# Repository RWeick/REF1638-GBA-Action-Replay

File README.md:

# REF1638-GBA-Action-Replay
The kicad files and firmware from the Datel GBA Action Replay board revision REF1638

PCB Thickness: 0.8 mm

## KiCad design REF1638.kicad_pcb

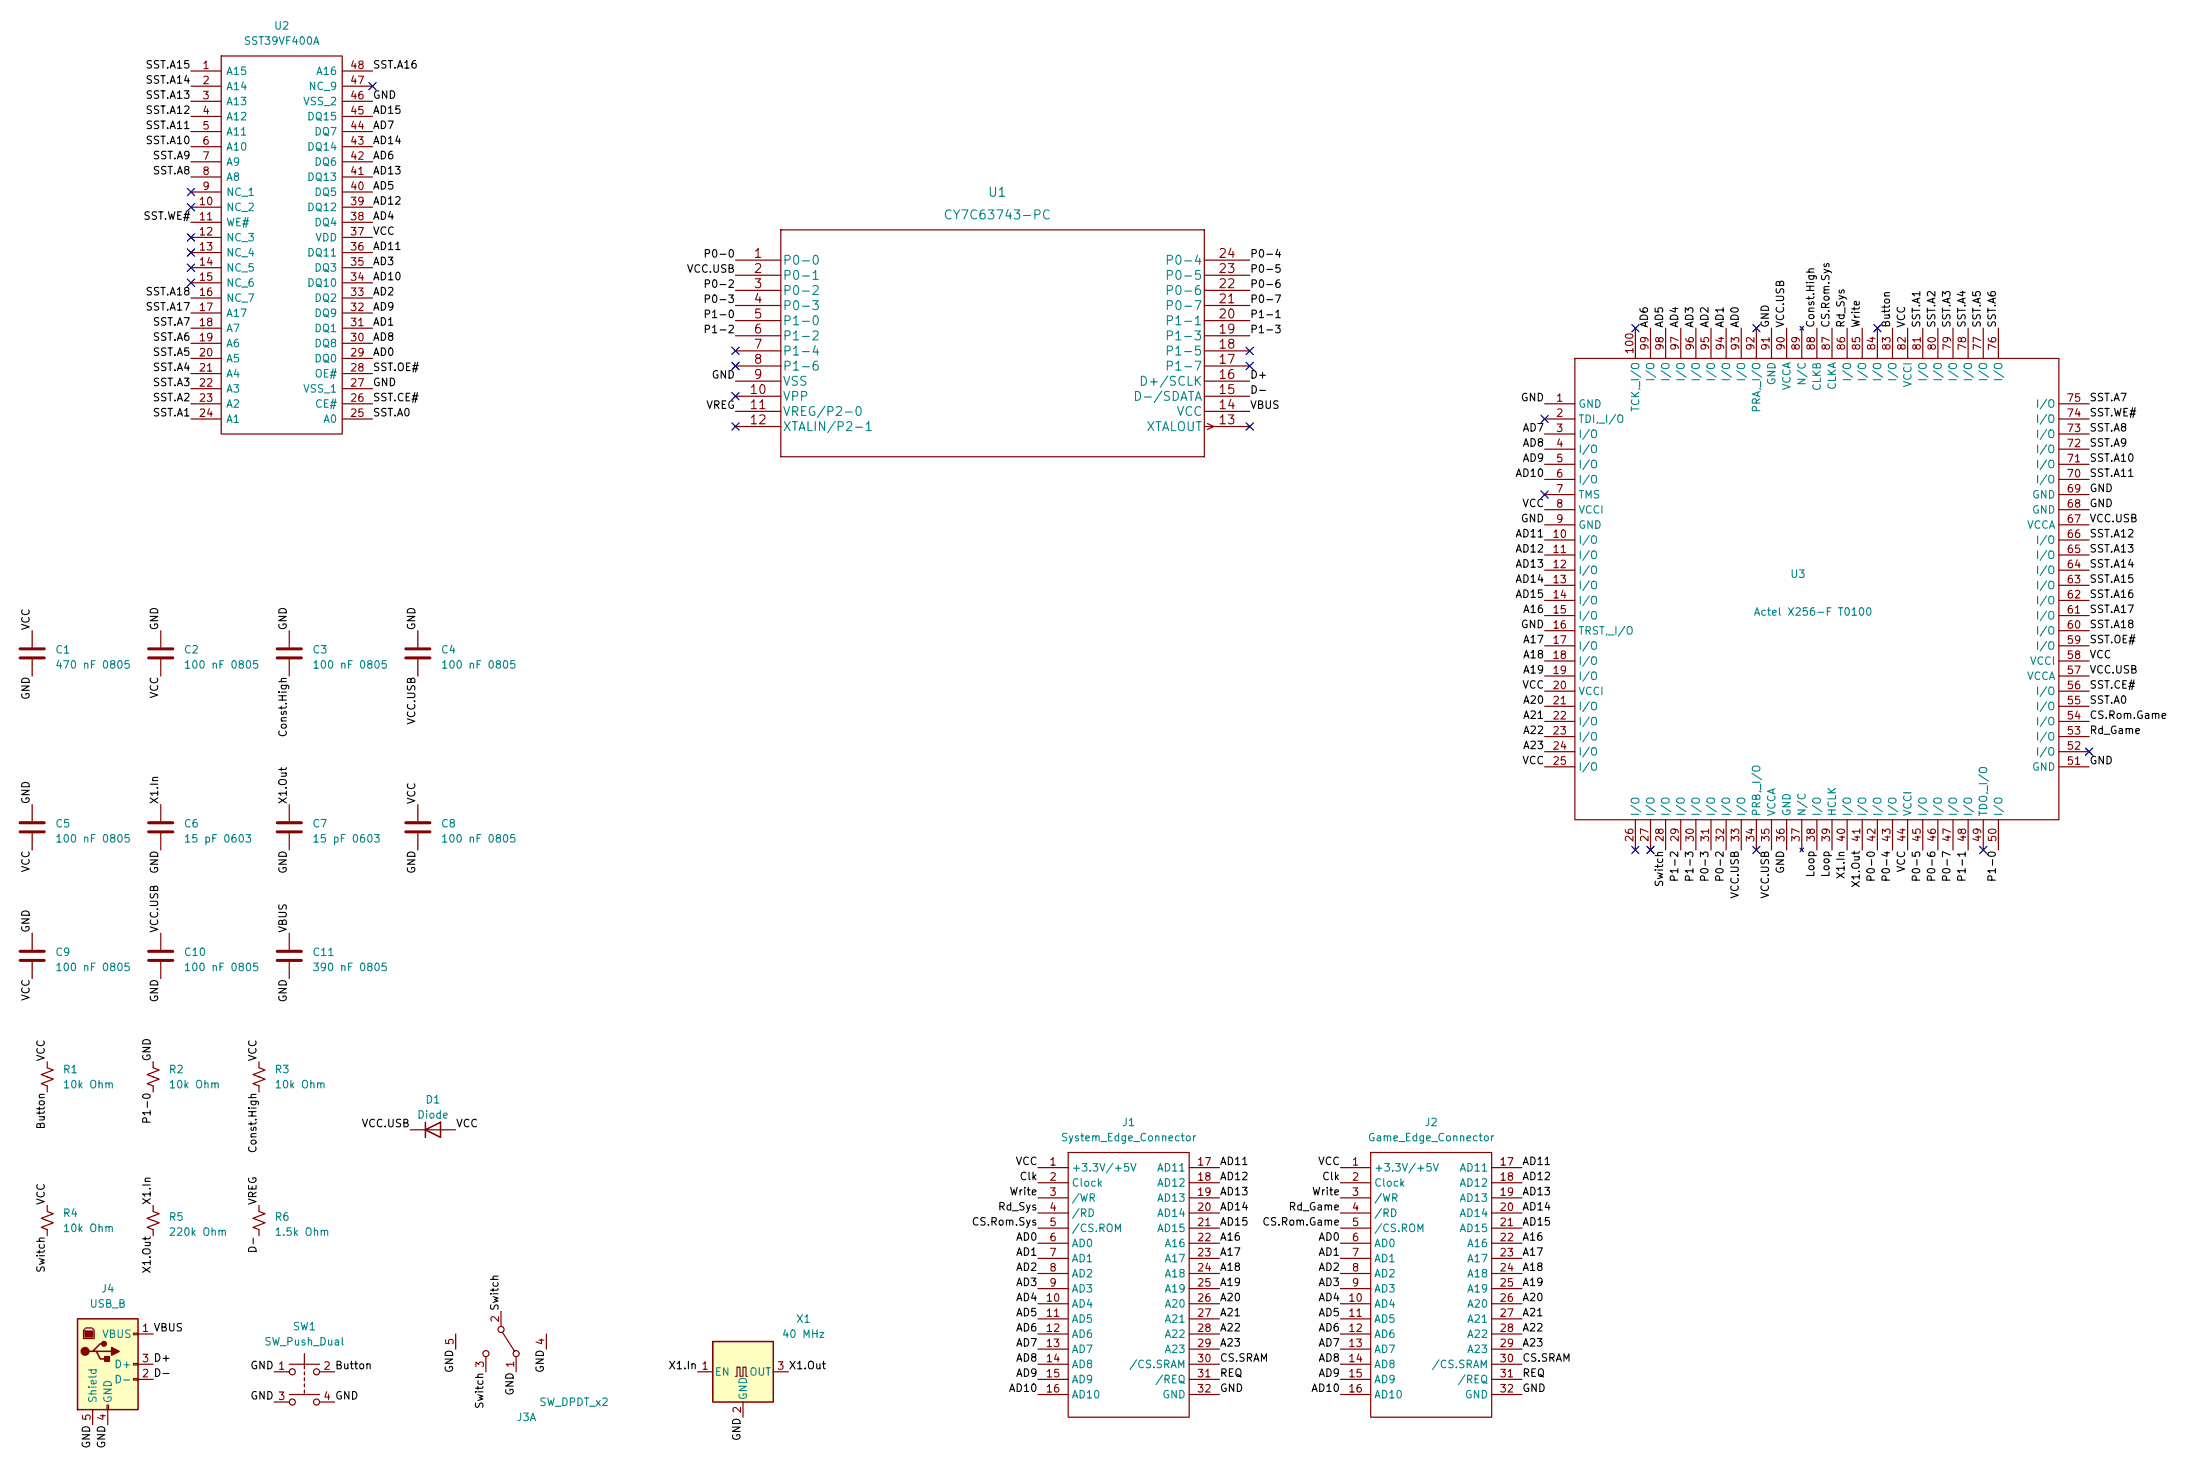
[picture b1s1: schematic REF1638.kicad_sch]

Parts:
C1: 470 nF 0805; Small SMD
C2, C3, C4, C5, C8, C9, C10: 100 nF 0805; Small SMD
C6, C7: 15 pF 0603; 0603 Caps
C11: 390 nF 0805; Small SMD
D1: Diode
J1: System_Edge_Connector; Edge Connector
J2: Game_Edge_Connector; Cartridge Slot, GBA
J3: SW_DPDT_x2; Switch_Wide
J4: USB_B; USB_B_OST_USB-B1HSxx_Horizontal
R1, R2, R3, R4: 10k Ohm; Small SMD
R5: 220k Ohm; Small SMD
R6: 1.5k Ohm; Small SMD
SW1: SW_Push_Dual; 1mm Side Push Button
U1: CY7C63743-PC; CY7C63743
U2: SST39VF400A; SST 39VF400A; Manufacturer_Part_Number SST39VF200A-70-4C-EKE
U3: Actel X256-F T0100; Actel X256-F
X1: 40 MHz; Crystal

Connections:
/A16: J1.22 (A16), J2.22 (A16), U3.15 (I/O)
/A17: J1.23 (A17), J2.23 (A17), U3.17 (I/O)
/A18: J1.24 (A18), J2.24 (A18), U3.18 (I/O)
/A19: J1.25 (A19), J2.25 (A19), U3.19 (I/O)
/A20: J1.26 (A20), J2.26 (A20), U3.21 (I/O)
/A21: J1.27 (A21), J2.27 (A21), U3.22 (I/O)
/A22: J1.28 (A22), J2.28 (A22), U3.23 (I/O)
/A23: J1.29 (A23), J2.29 (A23), U3.24 (I/O)
/AD0: J1.6 (AD0), J2.6 (AD0), U2.29 (DQ0), U3.93 (I/O)
/AD1: J1.7 (AD1), J2.7 (AD1), U2.31 (DQ1), U3.94 (I/O)
/AD2: J1.8 (AD2), J2.8 (AD2), U2.33 (DQ2), U3.95 (I/O)
/AD3: J1.9 (AD3), J2.9 (AD3), U2.35 (DQ3), U3.96 (I/O)
/AD4: J1.10 (AD4), J2.10 (AD4), U2.38 (DQ4), U3.97 (I/O)
/AD5: J1.11 (AD5), J2.11 (AD5), U2.40 (DQ5), U3.98 (I/O)
/AD6: J1.12 (AD6), J2.12 (AD6), U2.42 (DQ6), U3.99 (I/O)
/AD7: J1.13 (AD7), J2.13 (AD7), U2.44 (DQ7), U3.3 (I/O)
/AD8: J1.14 (AD8), J2.14 (AD8), U2.30 (DQ8), U3.4 (I/O)
/AD9: J1.15 (AD9), J2.15 (AD9), U2.32 (DQ9), U3.5 (I/O)
/AD10: J1.16 (AD10), J2.16 (AD10), U2.34 (DQ10), U3.6 (I/O)
/AD11: J1.17 (AD11), J2.17 (AD11), U2.36 (DQ11), U3.10 (I/O)
/AD12: J1.18 (AD12), J2.18 (AD12), U2.39 (DQ12), U3.11 (I/O)
/AD13: J1.19 (AD13), J2.19 (AD13), U2.41 (DQ13), U3.12 (I/O)
/AD14: J1.20 (AD14), J2.20 (AD14), U2.43 (DQ14), U3.13 (I/O)
/AD15: J1.21 (AD15), J2.21 (AD15), U2.45 (DQ15), U3.14 (I/O)
/Button: R1.2, SW1.2, U3.83 (I/O)
/CS.Rom.Game: J2.5 (/CS.ROM), U3.54 (I/O)
/CS.Rom.Sys: J1.5 (/CS.ROM), U3.87 (CLKA)
/CS.SRAM: J1.30 (/CS.SRAM), J2.30 (/CS.SRAM)
/Clk: J1.2 (Clock), J2.2 (Clock)
/Const.High: C3.2, R3.2, U3.88 (CLKB)
/D+: J4.3 (D+), U1.16 (D+/SCLK)
/D-: J4.2 (D-), R6.2, U1.15 (D-/SDATA)
/GND: C1.2, C2.1, C3.1, C4.1, C5.1, C6.2, C7.2, C8.2, C9.1, C10.2, C11.2, J1.32 (GND), J2.32 (GND), J3.1 (A), J3.4 (Case_GND), J3.5 (Case_GND), J4.4 (GND), J4.5 (Shield), R2.1, SW1.1, SW1.3, SW1.4, U1.9 (VSS), U2.27 (VSS_1), U2.46 (VSS_2), U3.1 (GND), U3.9 (GND), U3.16 (TRST,_I/O), U3.36 (GND), U3.51 (GND), U3.68 (GND), U3.69 (GND), U3.91 (GND), X1.2 (GND)
/Loop: U3.38 (I/O), U3.39 (HCLK)
/P0-0: U1.1 (P0-0), U3.42 (I/O)
/P0-2: U1.3 (P0-2), U3.32 (I/O)
/P0-3: U1.4 (P0-3), U3.31 (I/O)
/P0-4: U1.24 (P0-4), U3.43 (I/O)
/P0-5: U1.23 (P0-5), U3.45 (I/O)
/P0-6: U1.22 (P0-6), U3.46 (I/O)
/P0-7: U1.21 (P0-7), U3.47 (I/O)
/P1-0: R2.2, U1.5 (P1-0), U3.50 (I/O)
/P1-1: U1.20 (P1-1), U3.48 (I/O)
/P1-2: U1.6 (P1-2), U3.29 (I/O)
/P1-3: U1.19 (P1-3), U3.30 (I/O)
/REQ: J1.31 (/REQ), J2.31 (/REQ)
/Rd_Game: J2.4 (/RD), U3.53 (I/O)
/Rd_Sys: J1.4 (/RD), U3.86 (I/O)
/SST.A0: U2.25 (A0), U3.55 (I/O)
/SST.A1: U2.24 (A1), U3.81 (I/O)
/SST.A2: U2.23 (A2), U3.80 (I/O)
/SST.A3: U2.22 (A3), U3.79 (I/O)
/SST.A4: U2.21 (A4), U3.78 (I/O)
/SST.A5: U2.20 (A5), U3.77 (I/O)
/SST.A6: U2.19 (A6), U3.76 (I/O)
/SST.A7: U2.18 (A7), U3.75 (I/O)
/SST.A8: U2.8 (A8), U3.73 (I/O)
/SST.A9: U2.7 (A9), U3.72 (I/O)
/SST.A10: U2.6 (A10), U3.71 (I/O)
/SST.A11: U2.5 (A11), U3.70 (I/O)
/SST.A12: U2.4 (A12), U3.66 (I/O)
/SST.A13: U2.3 (A13), U3.65 (I/O)
/SST.A14: U2.2 (A14), U3.64 (I/O)
/SST.A15: U2.1 (A15), U3.63 (I/O)
/SST.A16: U2.48 (A16), U3.62 (I/O)
/SST.A17: U2.17 (A17), U3.61 (I/O)
/SST.A18: U2.16 (NC_7), U3.60 (I/O)
/SST.CE#: U2.26 (CE#), U3.56 (I/O)
/SST.OE#: U2.28 (OE#), U3.59 (I/O)
/SST.WE#: U2.11 (WE#), U3.74 (I/O)
/Switch: J3.2 (B), J3.3 (C), R4.2, U3.28 (I/O)
/VBUS: C11.1, J4.1 (VBUS), U1.14 (VCC)
/VCC: C1.1, C2.2, C5.2, C8.1, C9.2, D1.2 (A), J1.1 (+3.3V/+5V), J2.1 (+3.3V/+5V), R1.1, R3.1, R4.1, U2.37 (VDD), U3.8 (VCCI), U3.20 (VCCI), U3.25 (I/O), U3.44 (VCCI), U3.58 (VCCI), U3.82 (VCCI)
/VCC.USB: C4.2, C10.1, D1.1 (K), U1.2 (P0-1), U3.33 (I/O), U3.35 (VCCA), U3.57 (VCCA), U3.67 (VCCA), U3.90 (VCCA)
/VREG: R6.1, U1.11 (VREG/P2-0)
/Write: J1.3 (/WR), J2.3 (/WR), U3.85 (I/O)
/X1.In: C6.1, R5.1, U3.40 (I/O), X1.1 (EN)
/X1.Out: C7.1, R5.2, U3.41 (I/O), X1.3 (OUT)

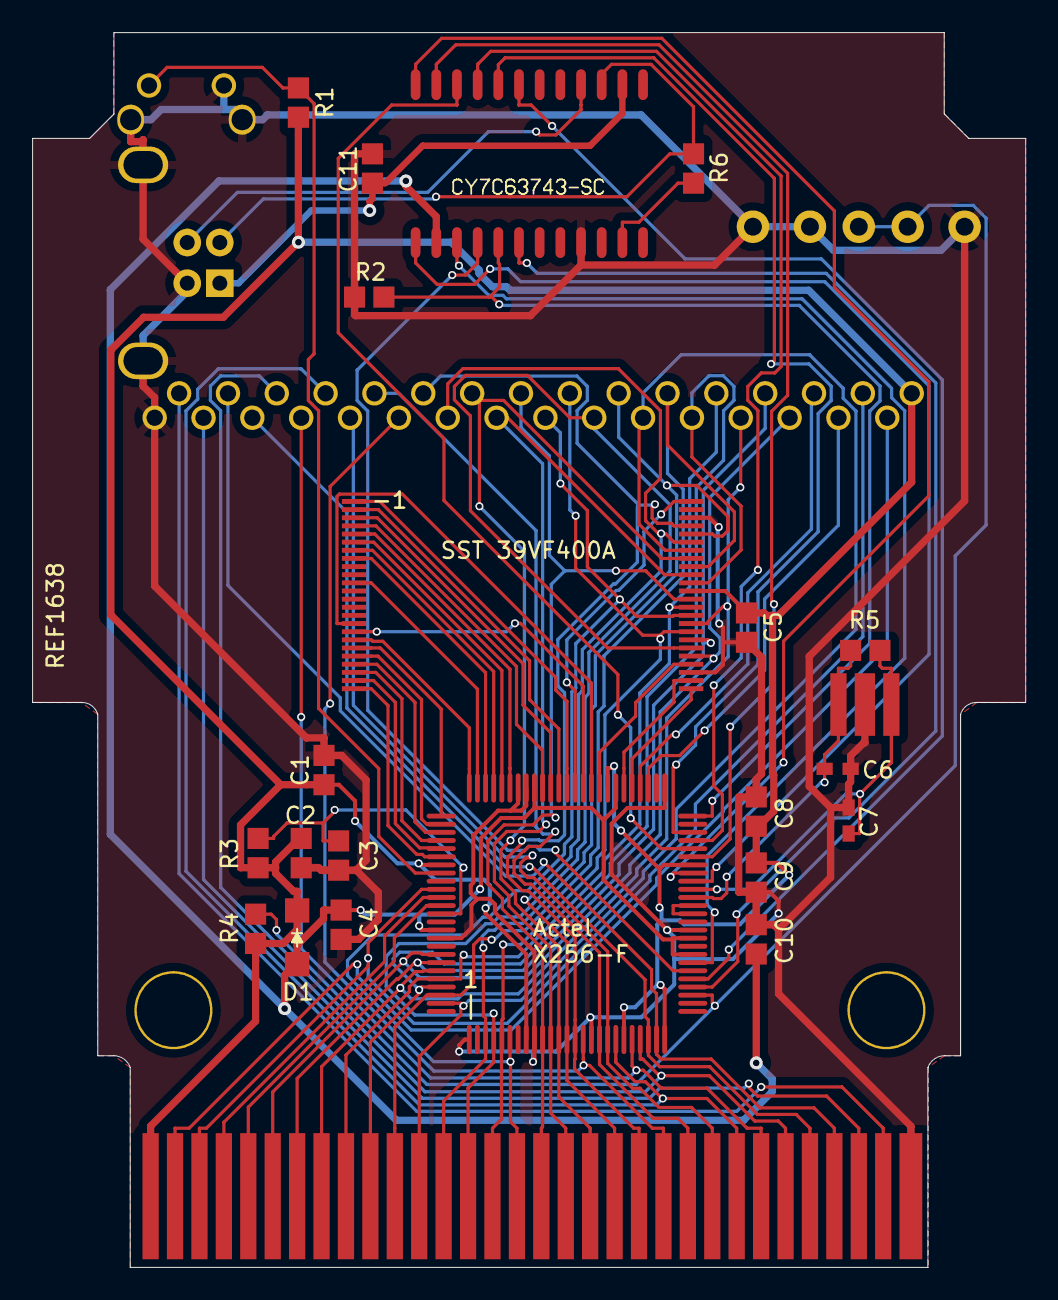
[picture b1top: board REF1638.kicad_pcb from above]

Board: 2 copper layers, 61.0 x 75.9 mm, 29 parts (0 on the bottom side), 78 nets.

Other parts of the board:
Hole1, Hole2: Hole
